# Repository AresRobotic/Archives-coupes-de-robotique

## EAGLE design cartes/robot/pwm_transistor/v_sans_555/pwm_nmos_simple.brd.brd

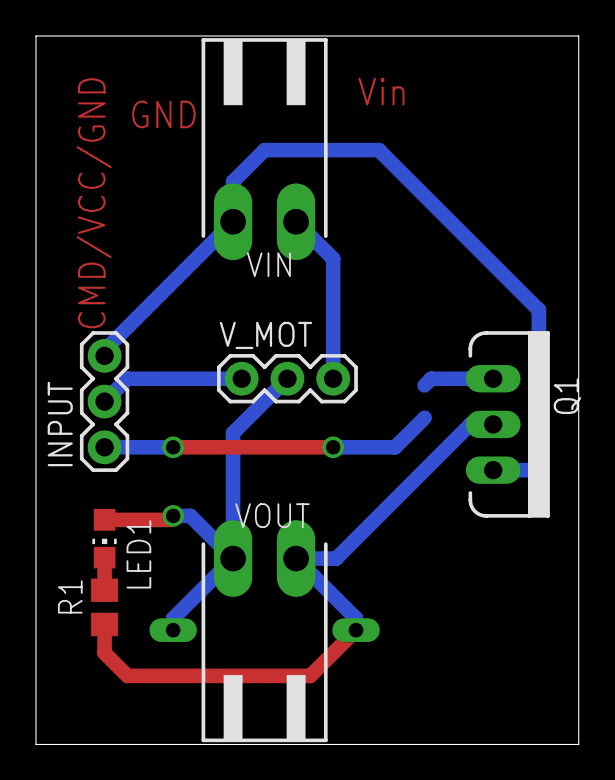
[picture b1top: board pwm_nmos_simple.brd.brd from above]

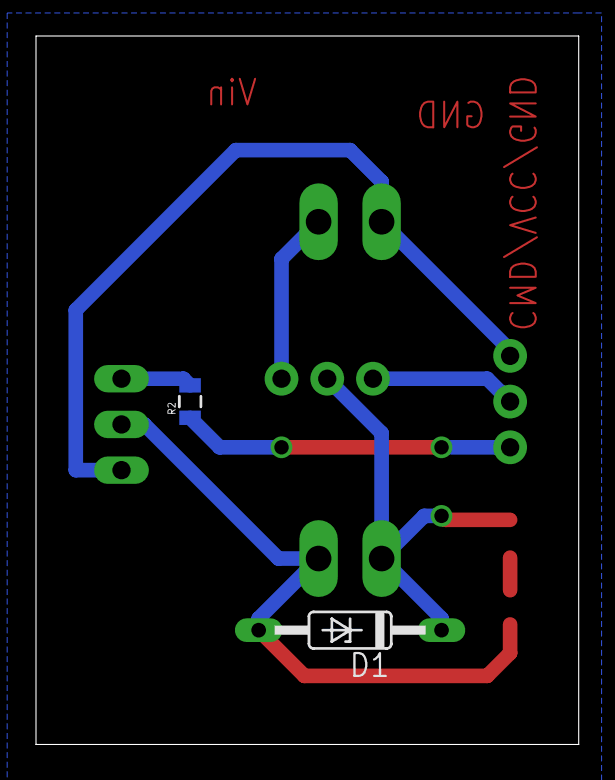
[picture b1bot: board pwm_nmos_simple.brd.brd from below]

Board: 2 copper layers, 30.1 x 39.4 mm, 9 parts (2 on the bottom side), 8 nets.

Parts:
D1: 1N821; DO35Z10
INPUT: 1X03
LED1: CHIP-LED0805
Q1: MOSFET-NCHANNELFQP30N06L; TO220V
R1: R0805
R2: 10ohm; 0805
VIN: 90-2
VOUT: 90-2
V_MOT: 1X03

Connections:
12V: VIN.1, V_MOT.3
CMD: INPUT.1, R2.1
GND: INPUT.3, Q1.3, VIN.2
unnamed: LED1.C, R1.2
unnamed: Q1.1, R2.2
unnamed: D1.A, Q1.2, R1.1, VOUT.2
V+_MOT: D1.C, LED1.A, VOUT.1, V_MOT.2
VCC: INPUT.2, V_MOT.1

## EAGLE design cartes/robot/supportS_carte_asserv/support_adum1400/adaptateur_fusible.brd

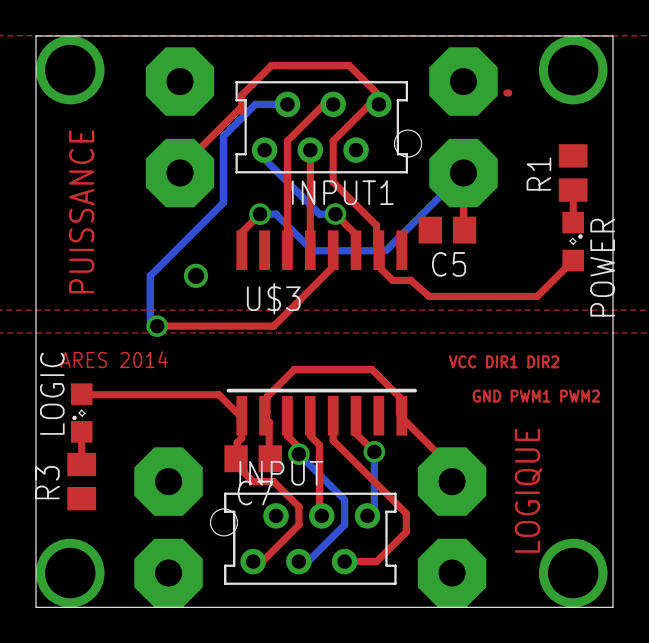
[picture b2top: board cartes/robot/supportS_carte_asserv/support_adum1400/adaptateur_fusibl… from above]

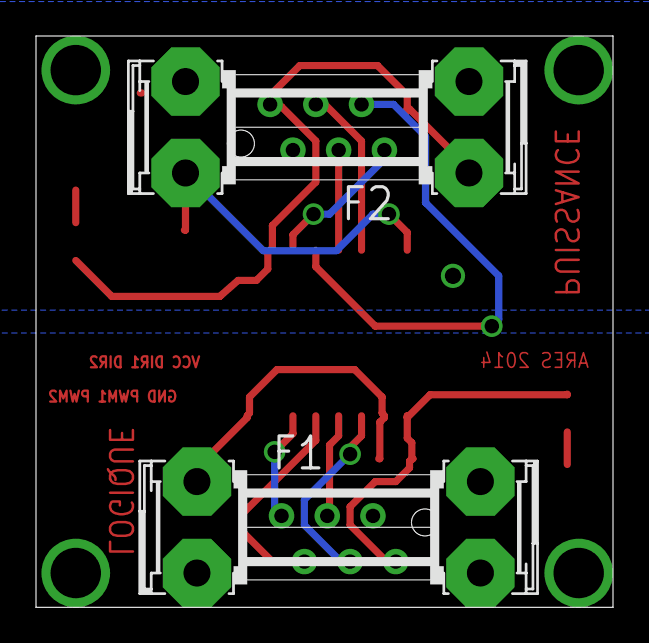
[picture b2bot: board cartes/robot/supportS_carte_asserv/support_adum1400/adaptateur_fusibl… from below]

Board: 2 copper layers, 32.1 x 31.7 mm, 11 parts (2 on the bottom side), 16 nets.

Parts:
C5, C7: 100nF; C0805
F1, F2: SHK20Q
INPUT, INPUT1: MMATCH-6-; AMP-215079-6
LOGIC: SML0805
POWER: SML0805
R1, R3: 1k; M0805
U$3: ADUM1400S; SO-16W

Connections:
+5V: F2.1A, INPUT1.1, POWER.A, U$3.10
C_DIR1: INPUT.3, U$3.3
C_DIR2: INPUT.5, U$3.5
C_PWM1: INPUT.4, U$3.4
C_PWM2: INPUT.6, U$3.6
DIR1: INPUT1.3, U$3.14
DIR2: INPUT1.5, U$3.12
GND: F1.2A, INPUT.2, R3.1
GNDA: C5.2, INPUT1.2, R1.2, U$3.9, U$3.15
unnamed: C7.1, F1.1A, U$3.2, U$3.8
unnamed: POWER.C, R1.1
unnamed: LOGIC.C, R3.2
unnamed: C5.1, F2.2A, U$3.16
PWM1: INPUT1.4, U$3.13
PWM2: INPUT1.6, U$3.11
VCC: C7.2, INPUT.1, LOGIC.A, U$3.1

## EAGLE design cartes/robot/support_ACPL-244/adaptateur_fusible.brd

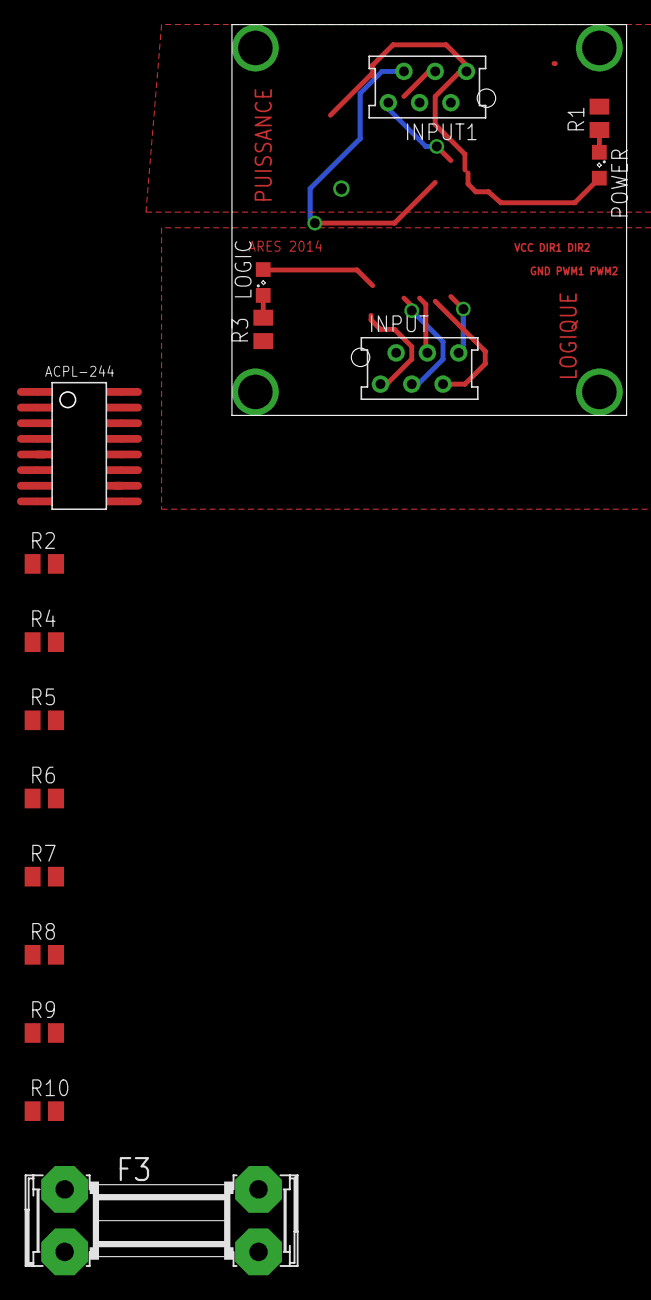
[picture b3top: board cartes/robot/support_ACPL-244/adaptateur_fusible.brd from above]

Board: 2 copper layers, 16 parts (0 on the bottom side), 21 nets.

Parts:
F3: SHK20Q
INPUT, INPUT1: MMATCH-6-; AMP-215079-6
LOGIC: SML0805
POWER: SML0805
R1, R2, R3, R4, R5, R6: 1k; M0805
R7, R8, R9, R10: 470; M0805
U$1: ACPL-244

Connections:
+5V: F3.2A, INPUT1.1, POWER.A
C_DIR1: INPUT.3, U$1.1
C_DIR2: INPUT.5, U$1.5
C_PWM2: INPUT.6, U$1.7
DIR1: INPUT1.3, R7.1
FUSE_5V: F3.1A, U$1.10, U$1.12, U$1.14, U$1.16
GND: INPUT.2, R2.2, R3.1, R4.2, R5.2, R6.2
GNDA: INPUT1.2, R1.2
unnamed: R2.1, U$1.2
unnamed: POWER.C, R1.1
unnamed: LOGIC.C, R3.2
unnamed: R4.1, U$1.4
unnamed: R5.1, U$1.6
unnamed: R6.1, U$1.8
unnamed: R7.2, U$1.15
unnamed: R8.2, U$1.13
unnamed: R9.2, U$1.11
unnamed: R10.2, U$1.9
PWM1: INPUT1.4, R8.1
PWM2: INPUT1.6, R10.1
VCC: INPUT.1, LOGIC.A

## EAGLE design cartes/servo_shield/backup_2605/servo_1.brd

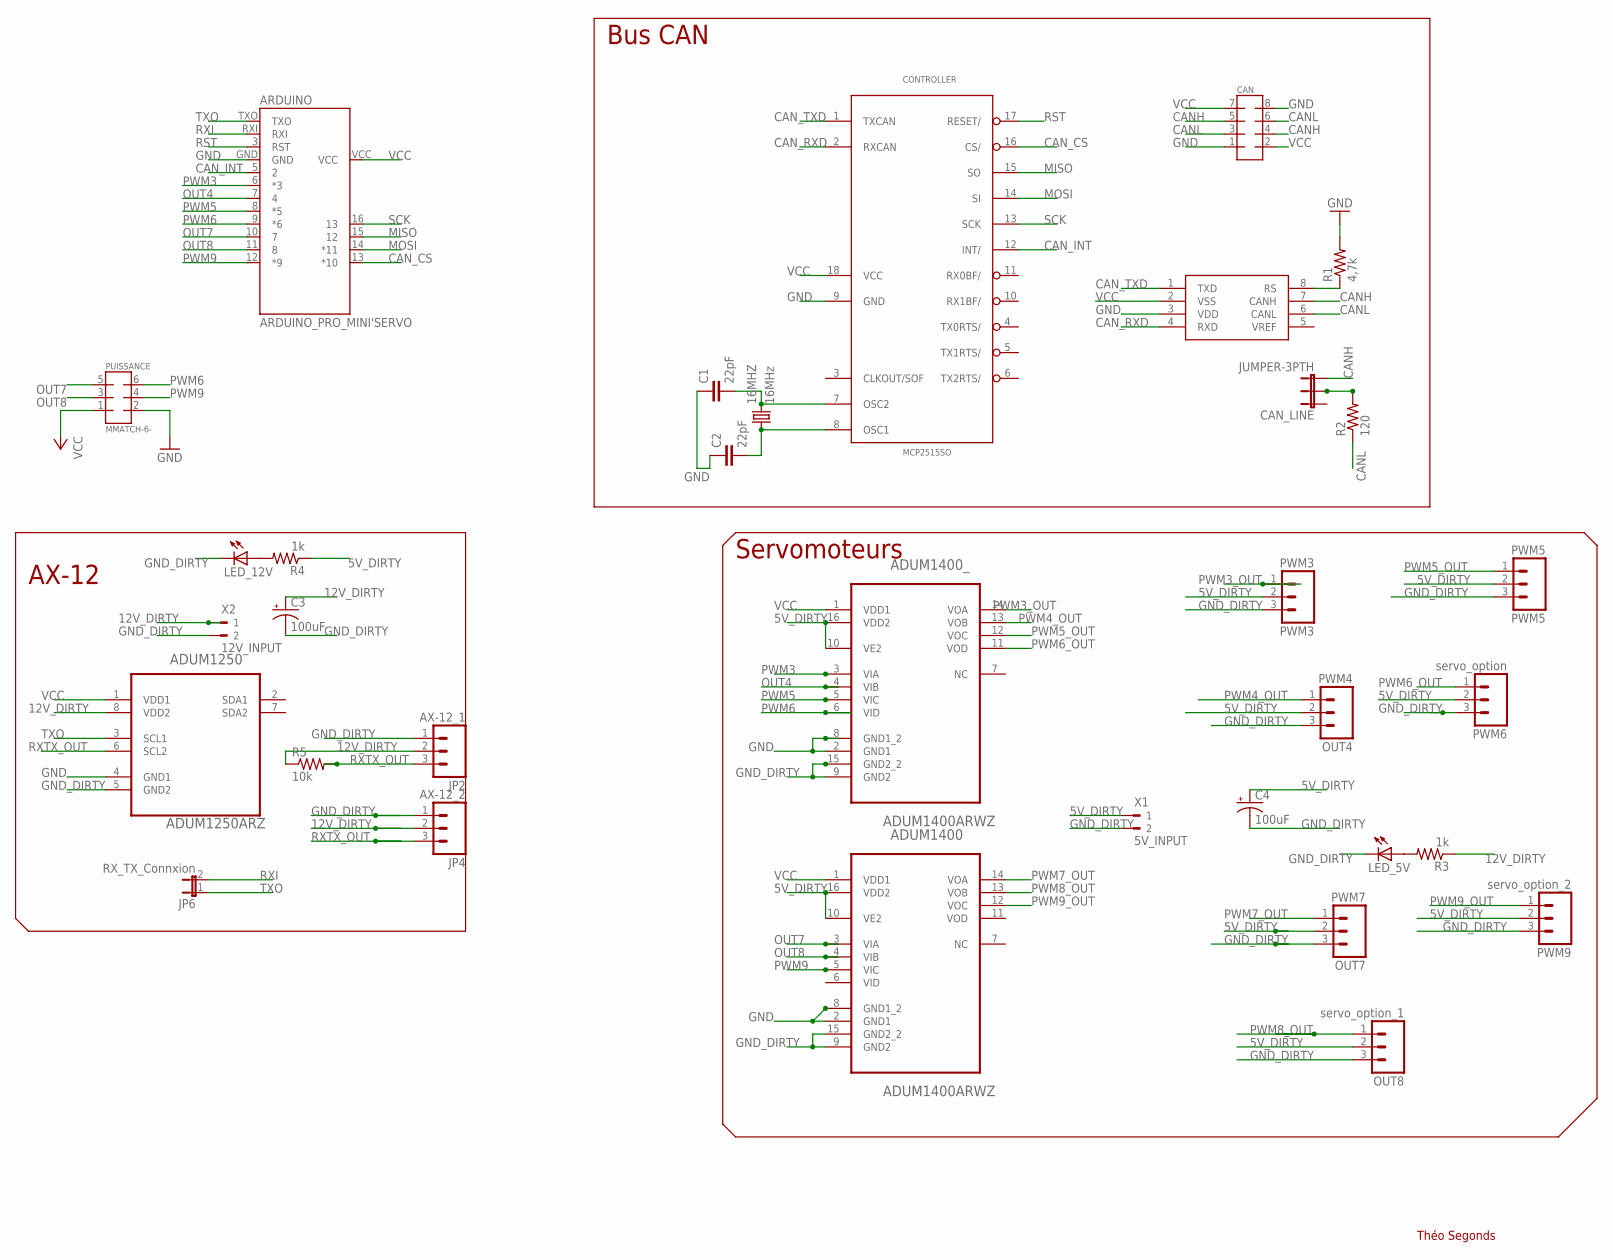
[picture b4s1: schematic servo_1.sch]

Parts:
16MHZ: 16MHz; HC49/S; MPN HC49SM-3.6864-30-50-60-16-ATF
ADUM1250: ADUM1250ARZ; SOIC127P600X175-8N
ADUM1400, ADUM1400_: ADUM1400ARWZ; SOIC127P1032X265-16N
ARDUINO: ARDUINO_PRO_MINI'SERVO; ARDUINO_PRO_MINI
C1, C2: 22pF; 0805; MPN 08055A220JAT2A
C3, C4: 100uF; CPOL-RADIAL-100UF-25V; MPN 100TXW100MEFC8X30
CAN: MMATCH-8-PTH; AMP-215079-8
CAN_LINE: JUMPER-3PTH; 1X03
CONTROLLER: MCP2515SO; SO18L
JP2: AX-12_1; MOLEX-1X3
JP4: AX-12_2; MOLEX-1X3
JP6: RX_TX_Connxion; 1X02
LED_5V, LED_12V: LEDCHIPLED_0805; CHIPLED_0805
OUT4: PWM4; 1X03
OUT7: PWM7; 1X03
OUT8: servo_option_1; 1X03
PUISSANCE: MMATCH-6-; AMP-215079-6
PWM3: PWM3; 1X03
PWM5: PWM5; 1X03
PWM6: servo_option; 1X03
PWM9: servo_option_2; 1X03
R1: 4,7k; 0805
R2: 120; 0805
R3, R4: 1k; 0805
R5: 10k; 0805
TRANSCEIVER: MCP2551; SO08; MPN MCP2551-I/SN...
X1: 5V_INPUT; 90-2
X2: 12V_INPUT; 90-2

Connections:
5V_DIRTY: ADUM1400.10 (VE2), ADUM1400.16 (VDD2), ADUM1400_.10 (VE2), ADUM1400_.16 (VDD2), C4.1 (+), OUT4.2, OUT7.2, OUT8.2, PWM3.2, PWM5.2, PWM6.2, PWM9.2, R4.1, X1.1
12V_DIRTY: ADUM1250.8 (VDD2), C3.1 (+), JP2.2, JP4.2, R3.1, R5.1, X2.1
CANH: CAN.4, CAN.5, CAN_LINE.3, TRANSCEIVER.7 (CANH)
CANL: CAN.3, CAN.6, R2.1, TRANSCEIVER.6 (CANL)
CAN_CS: ARDUINO.13 (*10), CONTROLLER.16 (CS/)
CAN_INT: ARDUINO.5 (2), CONTROLLER.12 (INT/)
CAN_RXD: CONTROLLER.2 (RXCAN), TRANSCEIVER.4 (RXD)
CAN_TXD: CONTROLLER.1 (TXCAN), TRANSCEIVER.1 (TXD)
GND: ADUM1250.4 (GND1), ADUM1400.2 (GND1), ADUM1400.8 (GND1_2), ADUM1400_.2 (GND1), ADUM1400_.8 (GND1_2), ARDUINO.GND, C1.1, C2.1, CAN.1, CAN.8, CONTROLLER.9 (GND), PUISSANCE.2 (4), R1.2, TRANSCEIVER.3 (VDD)
GND_DIRTY: ADUM1250.5 (GND2), ADUM1400.9 (GND2), ADUM1400.15 (GND2_2), ADUM1400_.9 (GND2), ADUM1400_.15 (GND2_2), C3.2 (-), C4.2 (-), JP2.1, JP4.1, LED_5V.C, LED_12V.C, OUT4.3, OUT7.3, OUT8.3, PWM3.3, PWM5.3, PWM6.3, PWM9.3, X1.2, X2.2
MISO: ARDUINO.15 (12), CONTROLLER.15 (SO)
MOSI: ARDUINO.14 (*11), CONTROLLER.14 (SI)
unnamed: 16MHZ.2, C1.2, CONTROLLER.7 (OSC2)
unnamed: 16MHZ.1, C2.2, CONTROLLER.8 (OSC1)
unnamed: LED_5V.A, R3.2
unnamed: R1.1, TRANSCEIVER.8 (RS)
unnamed: LED_12V.A, R4.2
unnamed: CAN_LINE.2, R2.2
OUT4: ADUM1400_.4 (VIB), ARDUINO.7 (4)
OUT7: ADUM1400.3 (VIA), ARDUINO.10 (7), PUISSANCE.5 (7)
OUT8: ADUM1400.4 (VIB), ARDUINO.11 (8), PUISSANCE.3 (5)
PWM3: ADUM1400_.3 (VIA), ARDUINO.6 (*3)
PWM3_OUT: ADUM1400_.14 (VOA), PWM3.1
PWM4_OUT: ADUM1400_.13 (VOB), OUT4.1
PWM5: ADUM1400_.5 (VIC), ARDUINO.8 (*5)
PWM5_OUT: ADUM1400_.12 (VOC), PWM5.1
PWM6: ADUM1400_.6 (VID), ARDUINO.9 (*6), PUISSANCE.6 (8)
PWM6_OUT: ADUM1400_.11 (VOD), PWM6.1
PWM7_OUT: ADUM1400.14 (VOA), OUT7.1
PWM8_OUT: ADUM1400.13 (VOB), OUT8.1
PWM9: ADUM1400.5 (VIC), ARDUINO.12 (*9), PUISSANCE.4 (6)
PWM9_OUT: ADUM1400.12 (VOC), PWM9.1
RST: ARDUINO.3 (RST), CONTROLLER.17 (RESET/)
RXI: ARDUINO.RXI, JP6.2
RXTX_OUT: ADUM1250.6 (SCL2), JP2.3, JP4.3, R5.2
SCK: ARDUINO.16 (13), CONTROLLER.13 (SCK)
TXO: ADUM1250.3 (SCL1), ARDUINO.TXO, JP6.1
VCC: ADUM1250.1 (VDD1), ADUM1400.1 (VDD1), ADUM1400_.1 (VDD1), ARDUINO.VCC, CAN.2, CAN.7, CONTROLLER.18 (VCC), PUISSANCE.1 (3), TRANSCEIVER.2 (VSS)

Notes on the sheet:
Bus CAN
AX-12
Servomoteurs
Théo Segonds

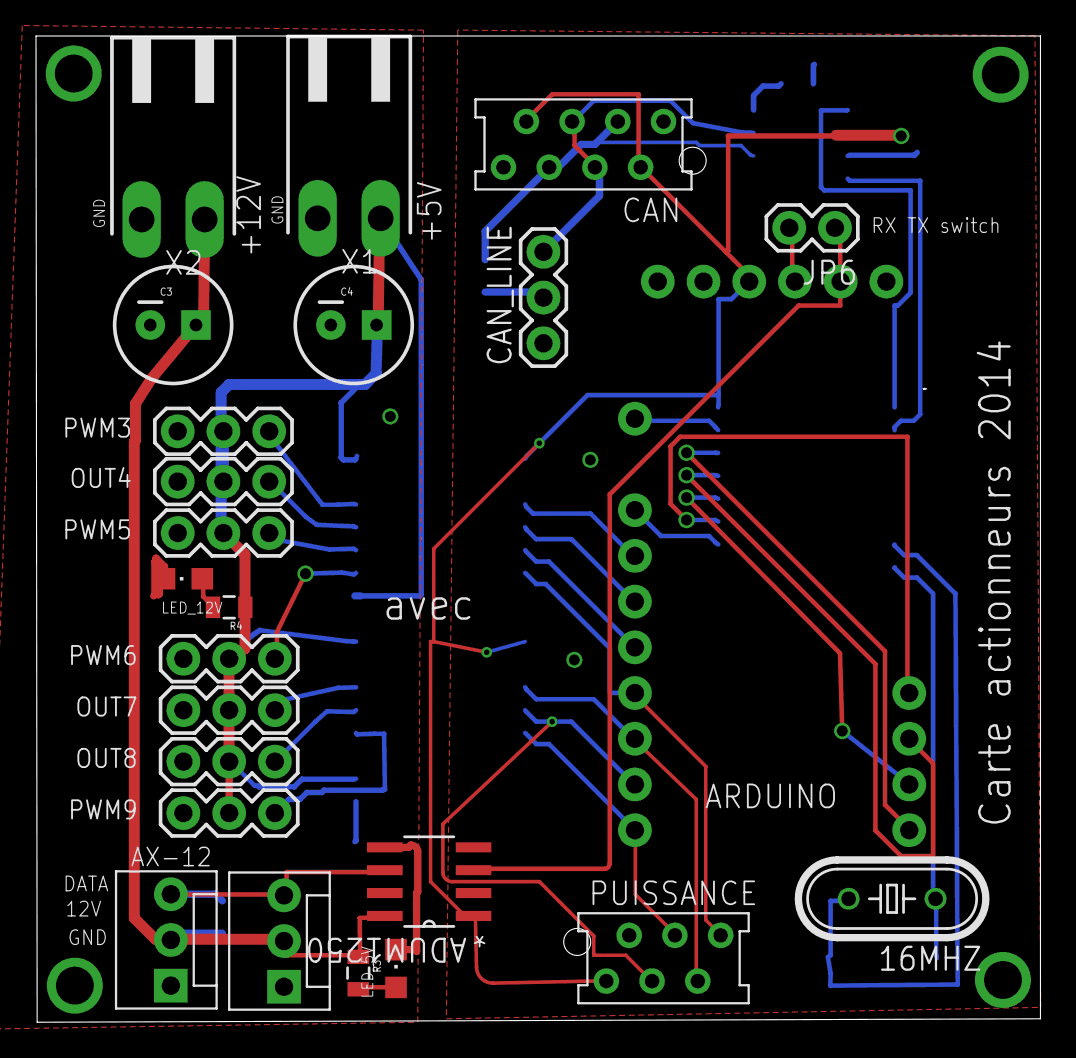
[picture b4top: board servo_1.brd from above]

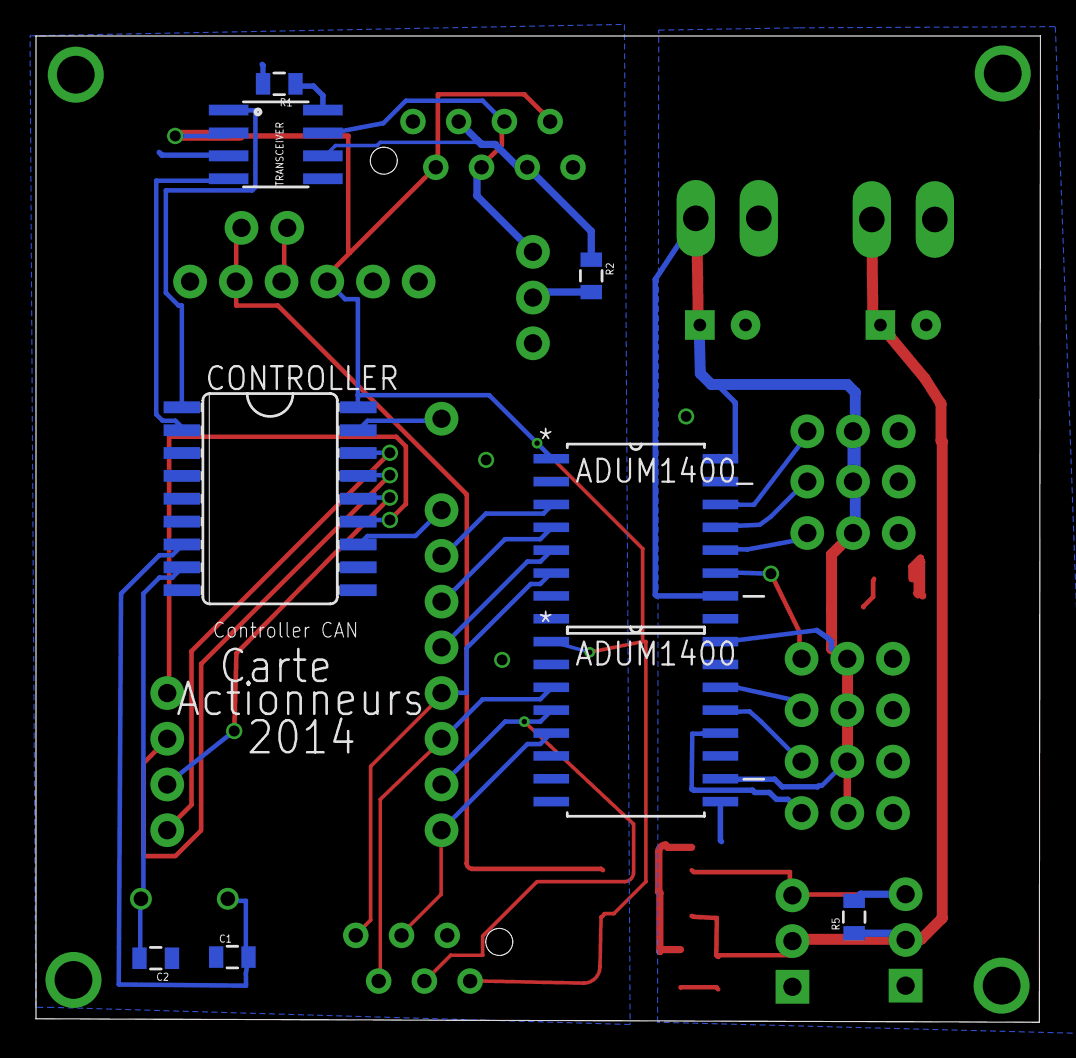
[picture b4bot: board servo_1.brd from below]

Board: 2 copper layers, 55.8 x 54.8 mm, 33 parts (9 on the bottom side), 38 nets.

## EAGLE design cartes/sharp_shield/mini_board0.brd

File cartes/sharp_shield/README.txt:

A vérifier et faire gerber
A utiliser avec http://code.google.com/p/rogue-code/wiki/SoftPWMLibraryDocumentation
Théo 24/04 à 23h40

Théo 26/04 : gerber fait, carte prête

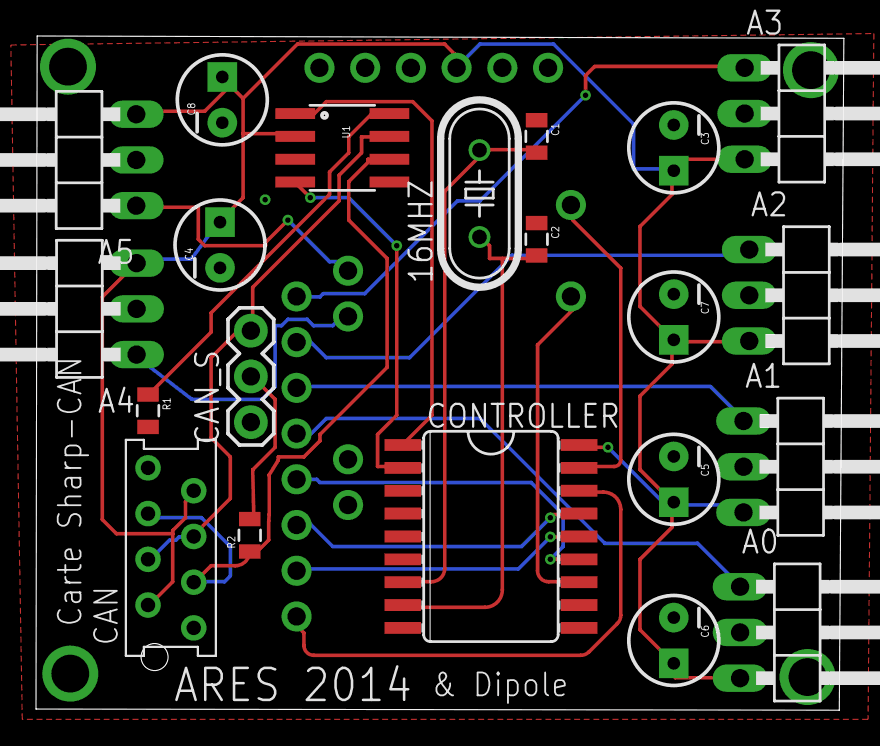
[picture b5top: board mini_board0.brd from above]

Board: 2 copper layers, 44.9 x 37.5 mm, 22 parts (1 on the bottom side), 22 nets.

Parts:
16MHZ: 16MHz; HC49/S
A0, A1, A2, A3, A4, A5: 1X03/90
ARDUINO: ARDUINO_PRO_MINI
C1, C2: 22pF; 0805
C3, C4, C5, C6, C7, C8: CPOL-RADIAL-10UF-25V
CAN: AMP-215079-8
CAN_S: JUMPER-3PTH; 1X03
CONTROLLER: MCP2515SO; SO18L
R1: 4,7k; 0805
R2: 120; 0805
U1: MCP2551; SO08

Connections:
A0: A0.1, ARDUINO.17
A1: A1.1, ARDUINO.18
A2: A2.1, ARDUINO.19
A3: A3.1, ARDUINO.20
A4: A4.1, ARDUINO.A4
A5: A5.1, ARDUINO.A5
CANH: CAN.4, CAN.5, CAN_S.3, U1.7
CANL: CAN.3, CAN.6, R2.1, U1.6
CAN_CS: ARDUINO.13, CONTROLLER.16
CAN_INT: ARDUINO.5, CONTROLLER.12
CAN_RXD: CONTROLLER.2, U1.4
CAN_TXD: CONTROLLER.1, U1.1
GND: A0.2, A1.2, A2.2, A3.2, A4.2, A5.2, ARDUINO.GND, C1.1, C2.1, C3.2, C4.2, C5.2, C6.2, C7.2, C8.2, CAN.1, CAN.8, CONTROLLER.9, R1.2, U1.3
MISO: ARDUINO.15, CONTROLLER.15
MOSI: ARDUINO.14, CONTROLLER.14
unnamed: 16MHZ.2, C1.2, CONTROLLER.7
unnamed: 16MHZ.1, C2.2, CONTROLLER.8
unnamed: R1.1, U1.8
unnamed: CAN_S.2, R2.2
RST: ARDUINO.3, CONTROLLER.17
SCK: ARDUINO.16, CONTROLLER.13
VCC: A0.3, A1.3, A2.3, A3.3, A4.3, A5.3, ARDUINO.VCC, C3.1, C4.1, C5.1, C6.1, C7.1, C8.1, CAN.2, CAN.7, CONTROLLER.18, U1.2

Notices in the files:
parts and their libraries:
SparkFun-DiscreteSemi: Licensing: CC v3.0 Share-Alike You are welcome to use this library for commercial purposes.
